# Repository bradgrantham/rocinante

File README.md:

# Introduction

I wired up a microcontroller on a protoboard to display video on a vintage CRT TV.

I call it Rocinante.

It's named after Don Quixote's horse in the novel by Miguel de Cervantes. Quixote is proud of his horse and views Rocinante as his noble steed that carries him boldy into battle.  Like Don Quixote, Rocinante is actually awkward, past his prime, and engaged in a task beyond his capabilities.

I reached the limit of what I could do comfortably on a protoboard, so I designed a PCB with the peripherals I thought I might need for a beefy version of the thing.  I had PCBWay make the boards and place the SMD parts.  The boards arrived November 4th, 2020.  I installed the through-hole parts myself.

# Hardware Features
* STM32H743IITX
* Power LED, debug LED, and RESET button
* BOOT button to reset into DFU mode
* 10-pin SWD (serial wire debugging) header
* USB connector for programming/device/host
* NTSC Composite video output
* Stereo audio output
* 3 "USER" buttons
* 3 programmable RGB LEDs (WS2812B aka "NeoPixel") and 3-pin header for chaining more
* Stereo audio input (untested)
* 2x PS/2 input (mouse, keyboard) (untested)
* 16-bit (R5G6B5) VGA output (untested)
* 166MHz 16MByte SDRAM (untested)
* 8-pin header compatible with ESP-01 for wireless (untested)
* SD card (untested)
* Expansion header with SPI and 2 GPIO
* I2S header

I'm keeping a spreadsheet of [the status of hardware features](https://docs.google.com/spreadsheets/d/15A8a8_nsbp0DDcee_6BzvSB4MXrgqT0VfsGb4YH8E2E/edit#gid=0) as I bring them up.

I'm keeping rework notes for Rev1 in [rework.md](rework.md).

# The Fundamental Idea

There is no framebuffer being directly scanned out in Rocinante.

Instead, there are two scanline buffers, and the CPU fills the next scanline buffer while DMA is scanning out the current scanline buffer.

Modern microcontrollers have high capabilities (the STM32H7 runs at 480MHz and has an FPU including double floats).  Embedded SRAM remains expensive, however, so most of the STM32 series doesn't contain enough RAM to display e.g. double-buffered 640x480 with 8-bit pixels.

This implementation trades CPU for memory and generates video data on-the-fly (aka "racing the beam") from a handful of different video formats at the time of writing:

* 1, 2, 4, and 8-bit palettized pixmaps
*  Monochrome text
* A "Wolfenstein"-style ray-casting maze renderer
* A display made of multiple run-length-compressed gradient spans per scanline

The current hardware supports a composite video display using NTSC output on an 8-bit DAC.  The pixel clock is 4x the color burst frequency, so typical console displays of the 1970's and 1980's should be almost directly representable.  Because the data is generated one scanline ahead and some CPU capacity is left over per scanline for apps, the latency for processing can be as low as one scanline.

Applications currently include a PPM viewer, PCM audio player, rudimentary 3D model viewer, and a very limited command shell.

I originally designed this with emulation of the Apple ][, ColecoVision, and Atari 2600 in mind, but who knows if I'll ever find the time for those!

# The Vision

## Hardware

On the PCB I also laid out a bunch of pie-in-the-sky features without knowing they would work.

The protoboard version used SPI to talk to an SD card.  The PCB wires an SD slot to the actual SDMMC signals on the STM32H7.

There's a 15-pin VGA header, two PS/2 jacks, and stereo audio input to give it some better media capabilities.

I daydreamed a system capable of running multiple simultaneous apps and installed 16 megabytes of SDRAM.

## Pipe Dream

Over time I hope I can make most of the system function.  If there's something that doesn't work but a fix is clear, maybe I'll spin a second rev of the board if I don't lose interest before then.

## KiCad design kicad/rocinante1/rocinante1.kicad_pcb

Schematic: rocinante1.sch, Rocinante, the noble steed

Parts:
BT1: 1225; BatteryHolder_Keystone_3001_1x12mm; Manufacturer PN 3001
C1, C2, C4, C6, C7, C8, C9, C10, C11, C12, C13, C14, C15, C16, C17, C21, C22, C23, C24, C28, C31, C32: 100nF; C_0603_1608Metric
C3, C5: 2.2µF; C_0603_1608Metric
C18, C19: 70nF; C_0603_1608Metric
C20: 1nF; C_0603_1608Metric
C25, C26, C27: 10µF; C_0603_1608Metric
C29, C30: 5.1pF; C_0603_1608Metric
C33, C35, C36: 1µF; C_0603_1608Metric
C34: 4.7µF; C_0603_1608Metric
D1: POWERLED; LED_0603_1608Metric; Manufacturer PN 150060GS75000
D2: DEBUGLED; LED_0603_1608Metric; Manufacturer PN 150060RS75000
D4: RGBLED1; LED_WS2812B_PLCC4_5.0x5.0mm_P3.2mm; Manufacturer PN WS2812B
D5: RGBLED2; LED_WS2812B_PLCC4_5.0x5.0mm_P3.2mm; Manufacturer PN WS2812B
D6: RGBLED3; LED_WS2812B_PLCC4_5.0x5.0mm_P3.2mm; Manufacturer PN WS2812B
F1: F_Small; Fuse_1210_3225Metric; Manufacturer PN 0ZCH0050FF2G
H1: HOLE0; MountingHole_3.2mm_M3_Pad_Via
H2: HOLE1; MountingHole_3.2mm_M3_Pad_Via
H3: HOLE2; MountingHole_3.2mm_M3_Pad_Via
H4: HOLE3; MountingHole_3.2mm_M3_Pad_Via
J1: ESP_01; PinSocket_2x04_P2.54mm_Vertical
J2: SWD; PinHeader_2x05_P1.27mm_Vertical_SMD; Manufacturer PN 20021521-00010C1LF
J3: COMPOSITE; CUI_RCJ-044; Manufacturer PN RCJ-044
J4: CTRL1; DSUB-9_Male_Horizontal_P2.77x2.84mm_EdgePinOffset7.70mm_Hou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; Manufacturer PN A-DS 09 A/KG-T2S
J5: CTRL2; DSUB-9_Male_Horizontal_P2.77x2.84mm_EdgePinOffset7.70mm_Hou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; Manufacturer PN A-DS 09 A/KG-T2S
J6: VGA; HD15-SN-24; Manufacturer PN HD15-SN-24
J7: AUDIOIN; Jack_3.5mm_CUI_SJ1-3535NG_Horizontal
J8: AUDIOOUT; Jack_3.5mm_CUI_SJ1-3535NG_Horizontal
J9: MOUSE; CUI_MD-60SM
J10: KEYBOARD; CUI_MD-60SM
J11: SERIAL; PinHeader_1x06_P2.54mm_Vertical
J12: SD_Card; 10067847-001RLF; Manufacturer PN 10067847-001RLF
J13: USBFS/POWER; USB_Micro-B_Amphenol_10104110_Horizontal; Manufacturer PN 10104110-0001LF
J14: I2S; PinHeader_1x06_P2.54mm_Vertical
J15: NEOPIXEL; PinHeader_1x03_P2.54mm_Vertical
J16: EXPHDR; PinHeader_2x05_P2.54mm_Vertical
Q1: Q_NPN_CBE; SOT-323_SC-70; Manufacturer PN MMBT3904WT1G
R1, R4: 220; R_0603_1608Metric
R2, R20, R28, R34: 2.2k; R_0603_1608Metric
R3: 6.8k; R_0603_1608Metric
R5: 215; R_0603_1608Metric
R6: 430; R_0603_1608Metric
R7: 860; R_0603_1608Metric
R8: 1.7k; R_0603_1608Metric
R9: 3.4k; R_0603_1608Metric
R10: 6.9k; R_0603_1608Metric
R11: 14k; R_0603_1608Metric
R12: 28K; R_0603_1608Metric
R13: 47; R_0603_1608Metric
R14, R15, R16, R21, R36, R37, R38, R39: 10K; R_0603_1608Metric
R17, R25, R31: 270; R_0603_1608Metric
R18, R26, R32: 560; R_0603_1608Metric
R19, R27, R33: 1100; R_0603_1608Metric
R22, R23, R43, R44, R45, R46, R47, R48: 20K; R_0603_1608Metric
R24, R29, R35: 4.3k; R_0603_1608Metric
R30: 8.6k; R_0603_1608Metric
R40, R41, R42: 150; R_0603_1608Metric
R49, R50, R51, R52, R53, R54: 68K; R_0603_1608Metric
R55, R56, R57, R58, R59, R60: 22; R_0603_1608Metric
R61, R62: 0; R_0603_1608Metric
SW1: RESET; SW_Push_1P1T_NO_6x6mm_H9.5mm; Manufacturer PN PTS645SM70SMTR92
SW2: USER1; SW_Push_1P1T_NO_6x6mm_H9.5mm; Manufacturer PN PTS645SM70SMTR92
SW3: USER2; SW_Push_1P1T_NO_6x6mm_H9.5mm; Manufacturer PN PTS645SM70SMTR92
SW4: USER3; SW_Push_1P1T_NO_6x6mm_H9.5mm; Manufacturer PN PTS645SM70SMTR92
SW5: BOOT0; SW_Push_1P1T_NO_6x6mm_H9.5mm; Manufacturer PN PTS645SM70SMTR92
TP1: CPST; TestPoint_Keystone_5015_Micro-Minature; Manufacturer PN RCW-0C
TP2: 5V; TestPoint_Keystone_5015_Micro-Minature; Manufacturer PN RCW-0C
TP3: 3V3; TestPoint_Keystone_5015_Micro-Minature; Manufacturer PN RCW-0C
TP4: GND; TestPoint_Keystone_5015_Micro-Minature; Manufacturer PN RCW-0C
TP5: KBDDATA; TestPoint_Keystone_5015_Micro-Minature; Manufacturer PN RCW-0C
TP6: KBDCLK; TestPoint_Keystone_5015_Micro-Minature; Manufacturer PN RCW-0C
U1: STM32H743IITx; LQFP-176_24x24mm_P0.5mm; Manufacturer PN STM32H743IIT6
U2: W9812G6KH-6; TSOP-II-54_22.2x10.16mm_P0.8mm; Manufacturer PN W9812G6KH-6
U3: LD1117S33TR_SOT223; SOT-223-3_TabPin2; Manufacturer PN LD1117S33TR
X1: ASE-14.31818MHz; Oscillator_SMD_Abracon_ASE-4Pin_3.2x2.5mm; Manufacturer PN ASEMB-14.31818MHZ-XY-T
Y1: 25MHz; Crystal_SMD_2016-4Pin_2.0x1.6mm; Manufacturer PN NX2016SA-25MHZ-EXS00A-CS11321

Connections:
ADC1_INP3: J7.T, U1.52
ADC1_INP5: J7.R, U1.57
ADC3_INP2: J4.9, U1.27
ADC3_INP3: J4.5, U1.25
ADC3_INP6: J5.9, U1.28
ADC3_INP7: J5.5, U1.26
AUDIO_OUT_L: C23.1, J8.T, R43.1
AUDIO_OUT_R: C24.1, J8.R, R44.1
BAT: BT1.1, C36.2, U1.6
BOOT: R21.1, SW5.2, U1.166
CLOCK0: R62.2, U1.29
CLOCK1: R61.2, U1.30
CV0: R12.2, U1.131
CV1: R11.2, U1.132
CV2: R10.2, U1.133
CV3: R9.2, U1.134
CV4: R8.2, U1.173
CV5: R7.2, U1.174
CV6: R6.2, U1.175
CV7: R5.2, U1.176
DAC1_OUT1: R22.2, U1.50
DAC1_OUT2: R23.2, U1.51
DEBUG: R4.1, U1.4
E1: J4.4, U1.86
E2: J5.4, U1.130
ESP_CH_EN: J1.4, U1.111
ESP_GPIO0: J1.5, R14.1
ESP_GPIO2: J1.3, R15.1
ESP_RST: J1.6, U1.110
ESP_RX: J1.7, U1.168
ESP_TX: J1.2, U1.11
EXPGPIO0: J16.8, U1.144
EXPGPIO1: J16.9, U1.145
EXPPWM: J16.7, U1.24
FIRE1: J4.6, U1.12
FIRE2: J5.6, U1.13
GND: BT1.2, C1.2, C2.2, C3.2, C4.2, C5.2, C6.2, C7.2, C8.2, C9.2, C10.2, C11.2, C12.2, C13.2, C14.2, C15.2, C16.2, C17.2, C18.2, C19.2, C20.2, C21.1, C22.1, C25.2, C26.2, C27.2, C28.1, C29.1, C30.1, C31.2, C32.1, C33.1, C34.2, C35.1, C36.1, D1.1 (K), D2.1 (K), D4.3, D5.3, D6.3, H1.1, H2.1, H3.1, H4.1, J1.1, J2.3, J2.5, J2.9, J4.0 (PAD), J5.0 (PAD), J6.0, J6.5, J6.6, J6.7, J6.8, J6.10, J7.S, J8.S, J9.3, J9.S1, J9.S2, J9.S3, J10.3, J10.S1, J10.S2, J10.S3, J11.6, J12.3, J12.6, J12.12, J12.13, J13.4, J13.5, J13.6, J14.6, J15.3, J16.6, R21.2, R40.1, R41.1, R42.1, R43.2, R44.2, SW1.1, TP4.1, U1.14, U1.22, U1.37, U1.48, U1.61, U1.71, U1.90, U1.102, U1.113, U1.126, U1.135, U1.148, U1.158, U2.6, U2.12, U2.28, U2.41, U2.46, U2.52, U2.54, U3.1, X1.2
I2C1_SCL: J6.15, U1.167
I2C1_SDA: J6.12, U1.165
I2S1_SDO: J14.3, U1.53
I2S_CK: J14.5, U1.154
I2S_SDI: J14.2, U1.152
I2S_WS: J14.4, U1.153
JOYSELECT: J4.7, J5.7, U1.58
KBD_CLK: J10.5, R38.1, R45.1, TP6.1
KBD_DATA: J10.1, R36.1, R46.1, TP5.1
KEYSELECT: J4.8, J5.8, U1.93
MOUSE_CLK: J9.5, R16.1, R47.1
MOUSE_DATA: J9.1, R37.1, R48.1
N1: J4.1, U1.83
N2: J5.1, U1.89
NRST: J2.10, SW1.2, U1.31
unnamed: C3.1, U1.125
unnamed: C5.1, U1.81
unnamed: C21.2, C23.2, R22.1
unnamed: C22.2, C24.2, R23.1
unnamed: C29.2, R61.1, Y1.1
unnamed: C30.2, R62.1, Y1.2
unnamed: D1.2 (A), R1.2
unnamed: D2.2 (A), R4.2
unnamed: D4.2, D5.4
unnamed: D4.4, Q1.1, R3.1
unnamed: D5.2, D6.4
unnamed: D6.2, J15.2
unnamed: F1.1, J13.1
unnamed: J12.1, R56.1
unnamed: J12.2, R57.1
unnamed: J12.5, R58.1
unnamed: J12.7, R59.1
unnamed: J12.8, R60.1
unnamed: J12.9, R55.1
unnamed: Q1.2, R2.1
unnamed: R39.1, X1.1
RGBLED_PWM: Q1.3, U1.5, U1.101
S1: J4.2, U1.84
S2: J5.2, U1.128
SDIO_CD: J12.10, U1.106
SDIO_CLK: R52.1, R58.2, U1.150
SDIO_CMD: R51.1, R57.2, U1.151
SDIO_D0: R53.1, R59.2, U1.94
SDIO_D1: R54.1, R60.2, U1.95
SDIO_D2: R49.1, R55.2, U1.161
SDIO_D3: R50.1, R56.2, U1.162
SDIO_WP: J12.11, U1.56
SDRAM_A0: U1.16, U2.23
SDRAM_A1: U1.17, U2.24
SDRAM_A2: U1.18, U2.25
SDRAM_A3: U1.19, U2.26
SDRAM_A4: U1.20, U2.29
SDRAM_A5: U1.21, U2.30
SDRAM_A6: U1.60, U2.31
SDRAM_A7: U1.63, U2.32
SDRAM_A8: U1.64, U2.33
SDRAM_A9: U1.65, U2.34
SDRAM_A10: U1.66, U2.22
SDRAM_A11: U1.67, U2.35
SDRAM_BA0: U1.108, U2.20
SDRAM_BA1: U1.109, U2.21
SDRAM_D0: U1.104, U2.2
SDRAM_D1: U1.105, U2.4
SDRAM_D2: U1.142, U2.5
SDRAM_D3: U1.143, U2.7
SDRAM_D4: U1.68, U2.8
SDRAM_D5: U1.69, U2.10
SDRAM_D6: U1.70, U2.11
SDRAM_D7: U1.73, U2.13
SDRAM_D8: U1.74, U2.42
SDRAM_D9: U1.75, U2.44
SDRAM_D10: U1.76, U2.45
SDRAM_D11: U1.77, U2.47
SDRAM_D12: U1.78, U2.48
SDRAM_D13: U1.96, U2.50
SDRAM_D14: U1.97, U2.51
SDRAM_D15: U1.98, U2.53
SDRAM_NBL0: U1.169, U2.15
SDRAM_NBL1: U1.170, U2.39
SDRAM_SDCKE0: U1.43, U2.37
SDRAM_SDCLK: U1.112, U2.38
SDRAM_SDNCAS: U1.160, U2.17
SDRAM_SDNE0: U1.44, U2.19
SDRAM_SDNRAS: U1.59, U2.18
SDRAM_SDNWE: U1.46, U2.16
SPI6_MISO: J16.1, U1.155
SPI6_MOSI: J16.4, U1.157
SPI6_NSS_SWCTL: J16.5, U1.107
SPI6_SCK: J16.3, U1.156
SWCLK: J2.4, U1.137
SWDIO: J2.2, U1.124
TIM1_CH2: U1.120, X1.3
TIM2_CH1: R45.2, U1.119, U1.138
TIM3_CH2: R47.2, U1.92, U1.163
TIM4_CH1: J6.13, U1.100
TIM5_CH2: J6.14, U1.88
USART1_RX: R46.2, U1.121, U1.164
USART2_CTS: J11.5, U1.40
USART2_RTS: U1.41
USART2_RX: J11.3, U1.47
USART2_TX: J11.2, U1.42
USART3_RX: R48.2, U1.79, U1.80
USB_FS_D_N: J13.2, U1.122
USB_FS_D_P: J13.3, U1.123
USER1: SW2.2, U1.1
USER2: SW3.2, U1.2
USER3: SW4.2, U1.3
VDD: C1.1, C2.1, C4.1, C6.1, C7.1, C8.1, C9.1, C10.1, C11.1, C12.1, C13.1, C14.1, C15.1, C16.1, C17.1, C18.1, C19.1, C25.1, C27.1, C31.1, C34.1, C35.2, J1.8, J2.1, J12.4, J14.1, J16.2, R1.1, R2.2, R13.1, R14.2, R15.2, R39.2, R49.2, R50.2, R51.2, R52.2, R53.2, R54.2, SW2.1, SW3.1, SW4.1, SW5.1, TP3.1, U1.15, U1.23, U1.36, U1.39, U1.49, U1.62, U1.72, U1.82, U1.91, U1.103, U1.114, U1.127, U1.136, U1.149, U1.159, U1.171, U1.172, U2.1, U2.3, U2.9, U2.14, U2.27, U2.43, U2.49, U3.2, X1.4
VGA_B0: R24.2, U1.32
VGA_B1: R20.2, U1.33
VGA_B2: R19.2, U1.34
VGA_B3: R18.2, U1.35
VGA_B4: R17.2, U1.54
VGA_BLUE: J6.3, R17.1, R18.1, R19.1, R20.1, R24.1, R40.2
VGA_G0: R30.2, U1.55
VGA_G1: R29.2, U1.115
VGA_G2: R28.2, U1.116
VGA_G3: R27.2, U1.117
VGA_G4: R26.2, U1.118
VGA_G5: R25.2, U1.139
VGA_GREEN: J6.2, R25.1, R26.1, R27.1, R28.1, R29.1, R30.1, R41.2
VGA_ID0: J6.11
VGA_ID2: J6.4
VGA_R0: R35.2, U1.140
VGA_R1: R34.2, U1.141
VGA_R2: R33.2, U1.8
VGA_R3: R32.2, U1.9
VGA_R4: R31.2, U1.10
VGA_RED: J6.1, R31.1, R32.1, R33.1, R34.1, R35.1, R42.2
VREFP: C32.2, C33.2, R13.2, U1.38
W1: J4.3, U1.85
W2: J5.3, U1.129

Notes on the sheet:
Compatible with Jim’s SPI header on pins 1-6
VDD DECOUPLING

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
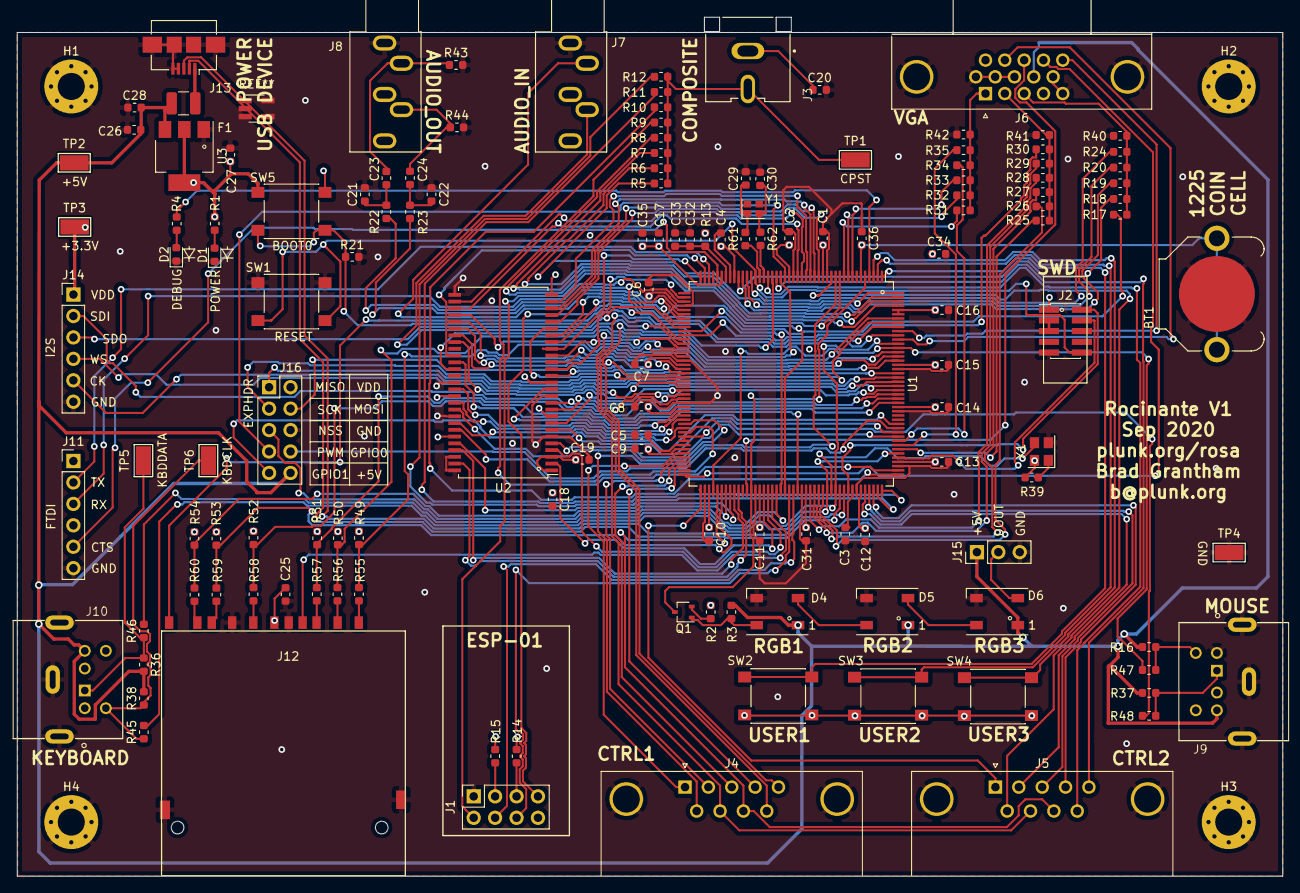
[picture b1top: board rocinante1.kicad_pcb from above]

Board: 4 copper layers, 150.0 x 101.8 mm, 142 parts (0 on the bottom side), 169 nets.

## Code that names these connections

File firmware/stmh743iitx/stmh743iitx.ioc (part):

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Mcu.Name=STM32H743IITx
Mcu.Package=LQFP176
Mcu.UserName=STM32H743IITx
PA0.Mode=CTS_RTS
PA0.Signal=USART2_CTS
PA1.Mode=CTS_RTS
PA1.Signal=USART2_RTS
PA10.Mode=Synchronous Slave
PA10.Signal=USART1_RX
PA11.Mode=Device_Only
PA11.Signal=USB_OTG_FS_DM
PA12.Mode=Device_Only
PA12.Signal=USB_OTG_FS_DP
PA13\ (JTMS/SWDIO).Mode=Serial_Wire
PA13\ (JTMS/SWDIO).Signal=DEBUG_JTMS-SWDIO
PA14\ (JTCK/SWCLK).Mode=Serial_Wire
PA14\ (JTCK/SWCLK).Signal=DEBUG_JTCK-SWCLK
PA15\ (JTDI).Signal=S_TIM2_CH1
PA2.Mode=Asynchronous
PA2.Signal=USART2_TX
PA3.Mode=Asynchronous
PA3.Signal=USART2_RX
PA4.Signal=COMP_DAC11_group
PA5.Signal=COMP_DAC12_group
PA6.Signal=ADCx_INP3
PA7.Mode=Full_Duplex_Master
PA7.Signal=I2S1_SDO
PA8.Mode=Synchronous Slave
PA8.Signal=USART1_CK
PA9.Signal=S_TIM1_CH2
PB0.Signal=GPIO_Input
PB1.Signal=ADCx_INP5
PB10.Mode=Synchronous Slave
PB10.Signal=USART3_TX
PB11.Mode=Synchronous Slave
PB11.Signal=USART3_RX
PB12.Mode=Synchronous Slave
PB12.Signal=USART3_CK
PB14.Mode=SD_4_bits_Wide_bus
PB14.Signal=SDMMC2_D0
PB15.Mode=SD_4_bits_Wide_bus
PB15.Signal=SDMMC2_D1
PB3\ (JTDO/TRACESWO).Mode=SD_4_bits_Wide_bus
PB3\ (JTDO/TRACESWO).Signal=SDMMC2_D2
PB4\ (NJTRST).Mode=SD_4_bits_Wide_bus
PB4\ (NJTRST).Signal=SDMMC2_D3
PB5.Signal=S_TIM3_CH2
PB6.Mode=Synchronous Slave
PB6.Signal=USART1_TX
PB7.Mode=I2C
PB7.Signal=I2C1_SDA
PB8.Mode=I2C
PB8.Signal=I2C1_SCL
PB9.Mode=Asynchronous
PB9.Signal=UART4_TX
PC0.Signal=GPIO_Output
PC1.Signal=GPIO_Output
PC10.Signal=GPIO_Output
PC11.Signal=GPIO_Output
PC12.Signal=GPIO_Output
PC13.Signal=GPIO_Output
PC14-OSC32_IN\ (OSC32_IN).Signal=GPIO_Output
PC15-OSC32_OUT\ (OSC32_OUT).Signal=GPIO_Output
PC2_C.Signal=GPIO_Output
PC3_C.Signal=GPIO_Output
PC4.Signal=GPIO_Output
PC5.Signal=GPIO_Output
PC6.Signal=GPIO_Output
PC7.Signal=GPIO_Output
PC8.Signal=GPIO_Output
PC9.Signal=GPIO_Output
PD0.Signal=FMC_D2_DA2
PD1.Signal=FMC_D3_DA3
PD10.Signal=FMC_D15_DA15
PD12.Signal=S_TIM4_CH1
PD13.Signal=S_TIM4_CH2
PD14.Signal=FMC_D0_DA0
PD15.Signal=FMC_D1_DA1
PD6.Mode=SD_4_bits_Wide_bus
PD6.Signal=SDMMC2_CK
PD7.Mode=SD_4_bits_Wide_bus
PD7.Signal=SDMMC2_CMD
PD8.Signal=FMC_D13_DA13
PD9.Signal=FMC_D14_DA14
PE0.Signal=FMC_NBL0
PE1.Signal=FMC_NBL1
PE10.Signal=FMC_D7_DA7
PE11.Signal=FMC_D8_DA8
PE12.Signal=FMC_D9_DA9
PE13.Signal=FMC_D10_DA10
PE14.Signal=FMC_D11_DA11
PE15.Signal=FMC_D12_DA12
PE2.Signal=GPXTI2
PE3.Signal=GPXTI3
PE4.Signal=GPXTI4
PE5.Signal=S_TIM15_CH1
PE6.Signal=S_TIM15_CH2
PE7.Signal=FMC_D4_DA4
PE8.Signal=FMC_D5_DA5
PE9.Signal=FMC_D6_DA6
PF0.Signal=FMC_A0
PF1.Signal=FMC_A1
PF10.Mode=IN6-Single-Ended
PF10.Signal=ADC3_INP6
PF11.Signal=FMC_SDNRAS
PF12.Signal=FMC_A6
PF13.Signal=FMC_A7
PF14.Signal=FMC_A8
PF15.Signal=FMC_A9
PF2.Signal=FMC_A2
PF3.Signal=FMC_A3
PF4.Signal=FMC_A4
PF5.Signal=FMC_A5
PF7.Mode=IN3-Single-Ended
PF7.Signal=ADC3_INP3
PF8.Mode=IN7-Single-Ended
PF8.Signal=ADC3_INP7
PF9.Mode=IN2-Single-Ended
PF9.Signal=ADC3_INP2
PG0.Signal=FMC_A10
PG1.Signal=FMC_A11
PG10.Mode=Full_Duplex_Master
PG10.Signal=I2S1_WS
PG11.Mode=Full_Duplex_Master
PG11.Signal=I2S1_CK
PG12.Mode=Full_Duplex_Master
PG12.Signal=SPI6_MISO
PG13.Mode=Full_Duplex_Master
PG13.Signal=SPI6_SCK
PG14.Mode=Full_Duplex_Master
PG14.Signal=SPI6_MOSI
PG15.Signal=FMC_SDNCAS
PG2.Signal=GPIO_Input
PG3.Signal=GPIO_Output
PG4.Signal=FMC_A14_BA0
PG5.Signal=FMC_A15_BA1
PG6.Signal=GPIO_Output
PG7.Signal=GPIO_Output
PG8.Signal=FMC_SDCLK
PG9.Mode=Full_Duplex_Master
PG9.Signal=I2S1_SDI
PH0-OSC_IN\ (PH0).Mode=HSE-External-Oscillator
PH0-OSC_IN\ (PH0).Signal=RCC_OSC_IN
PH1-OSC_OUT\ (PH1).Mode=HSE-External-Oscillator
PH1-OSC_OUT\ (PH1).Signal=RCC_OSC_OUT
PH11.Signal=S_TIM5_CH2
PH12.Signal=GPXTI12
PH13.Signal=GPXTI13
PH14.Signal=GPXTI14
PH15.Signal=GPXTI15
PH2.Mode=SdramChipSelect1_1
PH2.Signal=FMC_SDCKE0
PH3.Mode=SdramChipSelect1_1
PH3.Signal=FMC_SDNE0
PH5.Signal=FMC_SDNWE
PH6.Signal=GPXTI6
PH7.Signal=GPXTI7
PH8.Signal=GPXTI8
PH9.Signal=GPXTI9
PI0.Signal=GPIO_Output
PI1.Signal=GPIO_Output
PI2.Signal=GPIO_Output
PI3.Signal=GPIO_Output
PI4.Signal=GPIO_Output
PI5.Signal=GPIO_Output
PI6.Signal=GPIO_Output
PI7.Signal=GPIO_Output
PI9.Mode=Asynchronous
PI9.Signal=UART4_RX
RCC.SYSCLKFreq_VALUE=64000000
board=custom

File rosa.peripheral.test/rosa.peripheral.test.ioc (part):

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Mcu.Name=STM32H743IITx
Mcu.Package=LQFP176
Mcu.UserName=STM32H743IITx
PA11.Mode=Host_Only
PA11.Signal=USB_OTG_FS_DM
PA12.Mode=Host_Only
PA12.Signal=USB_OTG_FS_DP
PA13\ (JTMS/SWDIO).Mode=Serial_Wire
PA13\ (JTMS/SWDIO).Signal=DEBUG_JTMS-SWDIO
PA14\ (JTCK/SWCLK).Mode=Serial_Wire
PA14\ (JTCK/SWCLK).Signal=DEBUG_JTCK-SWCLK
PA15\ (JTDI).Signal=S_TIM2_CH1
PA2.Mode=Asynchronous
PA2.Signal=USART2_TX
PA3.Mode=Asynchronous
PA3.Signal=USART2_RX
PA9.GPIOParameters=GPIO_Speed
PA9.GPIO_Speed=GPIO_SPEED_FREQ_VERY_HIGH
PA9.Signal=S_TIM1_CH2
PB14.Mode=SD_4_bits_Wide_bus
PB14.Signal=SDMMC2_D0
PB15.Mode=SD_4_bits_Wide_bus
PB15.Signal=SDMMC2_D1
PB3\ (JTDO/TRACESWO).Mode=SD_4_bits_Wide_bus
PB3\ (JTDO/TRACESWO).Signal=SDMMC2_D2
PB4\ (NJTRST).Mode=SD_4_bits_Wide_bus
PB4\ (NJTRST).Signal=SDMMC2_D3
PB6.Signal=USART1_TX
PC0.Signal=FMC_SDNWE
PC2_C.Mode=SdramChipSelect1_1
PC2_C.Signal=FMC_SDNE0
PC3_C.Mode=SdramChipSelect1_1
PC3_C.Signal=FMC_SDCKE0
PD0.Signal=FMC_D2_DA2
PD1.Signal=FMC_D3_DA3
PD10.Signal=FMC_D15_DA15
PD14.Signal=FMC_D0_DA0
PD15.Signal=FMC_D1_DA1
PD6.Mode=SD_4_bits_Wide_bus
PD6.Signal=SDMMC2_CK
PD7.Mode=SD_4_bits_Wide_bus
PD7.Signal=SDMMC2_CMD
PD8.Signal=FMC_D13_DA13
PD9.Signal=FMC_D14_DA14
PE0.Signal=FMC_NBL0
PE1.Signal=FMC_NBL1
PE10.Signal=FMC_D7_DA7
PE11.Signal=FMC_D8_DA8
PE12.Signal=FMC_D9_DA9
PE13.Signal=FMC_D10_DA10
PE14.Signal=FMC_D11_DA11
PE15.Signal=FMC_D12_DA12
PE2.Mode=TX_Only_Simplex_Unidirect_Master
PE2.Signal=SPI4_SCK
PE3.GPIOParameters=GPIO_PuPd,GPIO_Label
PE3.GPIO_Label=USER2
PE3.GPIO_PuPd=GPIO_PULLDOWN
PE3.Signal=GPIO_Input
PE4.GPIOParameters=GPIO_PuPd,GPIO_Label
PE4.GPIO_Label=USER3
PE4.GPIO_PuPd=GPIO_PULLDOWN
PE4.Signal=GPIO_Input
PE5.GPIOParameters=GPIO_Label
PE5.GPIO_Label=DEBUG_LED
PE5.Signal=GPIO_Output
PE6.GPIOParameters=GPIO_Speed,GPIO_PuPd,GPIO_Label
PE6.GPIO_Label=RGBLED_SPI
PE6.GPIO_PuPd=GPIO_PULLDOWN
PE6.GPIO_Speed=GPIO_SPEED_FREQ_HIGH
PE6.Mode=TX_Only_Simplex_Unidirect_Master
PE6.Signal=SPI4_MOSI
PE7.Signal=FMC_D4_DA4
PE8.Signal=FMC_D5_DA5
PE9.Signal=FMC_D6_DA6
PF0.Signal=FMC_A0
PF1.Signal=FMC_A1
PF11.Signal=FMC_SDNRAS
PF12.Signal=FMC_A6
PF13.Signal=FMC_A7
PF14.Signal=FMC_A8
PF15.Signal=FMC_A9
PF2.Signal=FMC_A2
PF3.Signal=FMC_A3
PF4.Signal=FMC_A4
PF5.Signal=FMC_A5
PG0.Signal=FMC_A10
PG1.Signal=FMC_A11
PG15.Signal=FMC_SDNCAS
PG2.GPIOParameters=GPIO_PuPd,GPIO_Label
PG2.GPIO_Label=SDIO_CD
PG2.GPIO_PuPd=GPIO_PULLUP
PG2.Signal=GPIO_Input
PG4.Signal=FMC_A14_BA0
PG5.Signal=FMC_A15_BA1
PG8.Signal=FMC_SDCLK
PH0-OSC_IN\ (PH0).Mode=HSE-External-Oscillator
PH0-OSC_IN\ (PH0).Signal=RCC_OSC_IN
PH1-OSC_OUT\ (PH1).Mode=HSE-External-Oscillator
PH1-OSC_OUT\ (PH1).Signal=RCC_OSC_OUT
PI0.GPIOParameters=GPIO_Speed
PI0.GPIO_Speed=GPIO_SPEED_FREQ_MEDIUM
PI0.Signal=GPIO_Output
PI1.GPIOParameters=GPIO_Speed
PI1.GPIO_Speed=GPIO_SPEED_FREQ_MEDIUM
PI1.Signal=GPIO_Output
PI2.GPIOParameters=GPIO_Speed
PI2.GPIO_Speed=GPIO_SPEED_FREQ_MEDIUM
PI2.Signal=GPIO_Output
PI3.GPIOParameters=GPIO_Speed
PI3.GPIO_Speed=GPIO_SPEED_FREQ_MEDIUM
PI3.Signal=GPIO_Output
PI4.GPIOParameters=GPIO_Speed
PI4.GPIO_Speed=GPIO_SPEED_FREQ_MEDIUM
PI4.Signal=GPIO_Output
PI5.GPIOParameters=GPIO_Speed
PI5.GPIO_Speed=GPIO_SPEED_FREQ_MEDIUM
PI5.Signal=GPIO_Output
PI6.GPIOParameters=GPIO_Speed
PI6.GPIO_Speed=GPIO_SPEED_FREQ_MEDIUM
PI6.Signal=GPIO_Output
PI7.GPIOParameters=GPIO_Speed
PI7.GPIO_Speed=GPIO_SPEED_FREQ_MEDIUM
PI7.Signal=GPIO_Output
RCC.SYSCLKFreq_VALUE=480000000
RCC.SYSCLKSource=RCC_SYSCLKSOURCE_PLLCLK
board=custom

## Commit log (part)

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2020-04-25 clean up
    use normal getchar and setvbuf for single-key input
    add variables to Makefile for compiling and adding microray
    retire DAC issue in notes , add some more TODOs
    use TIM9 in DMA IRQ Handler, clean up slightly
2020-04-25 remove SERIAL_flush
2020-04-25 specify flash is slow; fix microray variables
2020-04-25 be draconian with min heap size; will force less .data and .bss
2020-04-25 allow 4 files to reduce memory use
2020-04-25 putting scanling info in normal RAM doesn't make things worse
2020-04-27 enable TIM9
2020-04-27 hosted application driver; WIP
2020-04-27 Remove unnecessary SERIAL_flush
2020-04-27 Add some more notes on optimization
2020-04-28 add notes on filtering and threading
2020-04-28 make main.o a regular object, add separate wolftextures
2020-04-29 add waveforms of different frequencies
2020-04-29 add initial support for STM32F746
2020-04-30 get SD working; reenable FatFS
2020-05-02 make hosted vehicle C++
2020-05-02 return to previous stack carveout
2020-05-02 video works
2020-05-02 update to match TIM1 clock in STM324F746
2020-05-05 include the F7 version of the SDK
2020-05-05 enable dcache; enable audio; enable FIFO threshold; fix row cycle counts
2020-05-06 notes on GLFW integration
2020-05-08 use float for interpolants, needs speeding up
2020-05-12 add comparison of pixel rows fill by segments
2020-05-12 Add a segment test
2020-05-12 make everything take a ...Segment
2020-05-12 fix bug, add drawing spheres
2020-05-13 add and use segment pool
2020-05-13 use segment_utility for circles in segtest
2020-05-13 fix circles; add VideoBufferReset
2020-05-13 make new segment utilities
2020-05-20 move main to C++, restructure VRAM, improve show and segment test
    output slightly more correct clocks but still wrong in clocks.py
    make colorburst waveform more closely match Apple 2 by increasing number and moving slightly earlier
    fix incorrect args parsing in showimage.c
    print the largest allocatable before each command prompt
    beef up .gitignores
    add BASIC programs I'd like to run
2020-05-22 make all warnings cause an error
2020-05-22 remove incorrect RAM note
2020-06-04 Add missing files
2020-06-05 stub rasterization if not HOSTED
2020-06-06 fix GL lighting
2020-06-07 add notes on closing out segmented mode
2020-06-07 add depth buffering, name Rasterizer API better
2020-06-16 fix phrasing
2020-06-18 defer trapezoids from triangles; render trapezoids
2020-06-18 use smaller structs, delete unused code
2020-06-21 get some statistics on trapezoid segments; store in notes
2020-06-25 add lots more notes on windowing
2020-06-25 make array-list operations into member functions
2020-06-30 factor out IsEmpty, improve scanline check; better stats
2020-07-08 Add more models and converters, add aspect ratio, more segmented video
2020-08-16 remove old boot.bin target, add note about st-flash
2020-08-16 calculate target, add measured HSE
2020-08-16 Add more clocks for discovery mode
    Also Add aspect ratio of segmented video mode
    Also output HSE/5 on MCO2
2020-08-16 add 3D rendering through segments
2020-08-16 add binaries
2020-08-16 STM32H745IGTx library for KiCad
2020-08-18 add notes on ETR experiment
2020-08-30 use floats for better register availability
2020-08-30 add most of schematic for Rosa v1
2020-09-06 remove stray vi command
2020-09-08 finish schematic draft; place some parts
2020-09-13 put tests and tools in better-named directory
2020-09-13 checkpoint clocks script
2020-09-13 add DAC line but commented, note current DAC max
2020-09-13 add more notes
2020-09-14 add span windowing test
2020-09-19 add first revision of PCB
2020-09-21 add some necessary BOM fields
2020-09-23 factor out some ntsc and dac functionality
2020-10-06 Checkpoint video subsystem rewrite
    Move NTSC constants out
    Disable all but 40x24 text and 8-bit overscan mode temporarily
2020-10-09 checkpoint video rewrite
2020-10-10 Add de-chroma test
2020-10-10 add initial Window stubs
2020-10-11 add attempt at decoding NTSC signal at DAC
2020-10-20 checkpoint showimage work on video rewrite
2020-10-24 add draft spans in WindowCreate plus palette functions
2020-10-25 move to scanline ranges
2020-10-31 add window span code to hosted, disable old driver methods
2020-11-02 store NTSC structures in VRAM
2020-11-06 add Rosa bringup test program
2020-11-06 fix label placement
2020-11-06 USART2 test
2020-11-06 update to bringup of PCB
2020-11-07 checkpoint work on RGB LEDs; 3X SPI sort of working
2020-11-08 WS2812Bs demonstrated working
    Using blocking SPI transmit at the moment
    SPI4 uses PE2 and PE6, which means USER1 button isn't currently read.
    Demo
    RGB1 red on and off, cycling every second.
    RGB2 rotates through hue every pi*2 seconds
    RGB3 rises from off to white over one second and back to off over one second
2020-11-08 use lower max value for RGB animation test
2020-11-08 add V1 image
2020-11-08 additional demo images
2020-11-10 save failed PS/2 TIM experiments for reference
2020-11-12 add more lines of top-level docs brainstorm
2020-11-15 add GPIOI DAC test
2020-11-16 NTSC works marginally
2020-11-17 fix cap at composite out
2020-11-17 add rework notes
2020-11-17 fix link to rework
2020-11-17 add tool to make blob for composite scanout
2020-11-17 add video test - subject is Millie the dog
2020-11-18 Move to 912 samples to be a multiple of colorburst
2020-11-22 output a const array; more likely to go into ROM
2020-11-22 add ProcessYield prototype
2020-11-22 do interlaced NTSC
2020-11-22 add scale functions
2020-11-22 use scale functions in show app
2020-11-22 implement pixmap fillRow
2020-11-22 update notes
2020-11-24 fix crash by not using iterator
2020-11-24 put more debug guards around dumps and prints
2020-11-27 lay groundwork for moveAllocation
2020-11-28 make window status be or'd bitfields
    And add the ability to set maximum pixel scale in showimage
2020-11-30 Add mouse pointer and fix NTSC decoding
2020-12-05 checkpoint apple2e emulator hack
2020-12-05 clean up
    change sprintf(message) etc to printf
    turn on scanout mark
    optimize Woz HGR fillrow
    tell apple2 to go "-fast"
    some constexprs
    temporarily turn off audio fill
2020-12-06 initial notes; user buttons
2020-12-06 remove unused array, fix missing return value
2020-12-08 Add events and keyboard processing and tests
    Also add NTSC func ptr switch function and "valid" flag
    Maybe fix the strange colors in HGR mode
    Add text and HGR mode tests
2020-12-09 put into tree so that I know if MX changes this
2020-12-09 Add tools for experimenting with dithered Apple //e DHGR
2020-12-09 add mouse processing
    move keyboard.{cpp,h} to hid*
    Also enable SDMMC for next experiments
2020-12-10 update with SDMMC and FATFS
2020-12-10 add FATFS, SDMMC, and a test for SD
2020-12-12 increase heap
2020-12-13 Add rework for USER1
2020-12-13 make output const
2020-12-13 fix ampersand
2020-12-13 add initial keyboard support to apple2e
2020-12-13 keyboard fixes, interactive apple 2
    use key repeat manager
    launch apple2e emulator in interactive mode,
    don't prepopulate key buffer with program
    enable DMA for SPI4
    increase heap size in MX project to match hand-coded
2020-12-13 upgrade version
2020-12-13 more diffusion methods, vec3f type
2020-12-13 squelch ABI warning
2020-12-13 fix warning
2020-12-13 Fix some keyboard processing
    Fix keyboard release in apple2e
    Fix repeat processing idiom
    And clean up some warnings
    F12 is RESET in Apple2e
    LEFT Win (GUI) is left APPLE so Win-F12 is REBOOT
2020-12-14 fix CTRL in apple2e
2020-12-14 test audio; provide app LED interface
2020-12-15 add RoDebugOverlayPrintf, rename LEDSet, SDMMC divider 5
2020-12-15 clear floppy drive light on RESET
2020-12-20 Remove unused variable
2020-12-20 add my version of Jim's script for running gdb-server over SWD
2020-12-28 Make apple2e audio work and floppy fast,
    Fix code to avoid warnings
    Shrink heap slightly to fit data
    Update to main apple2e emulator source at 43c3c8a
    Update to improved cpu6502 emulator source at 43c3c8a
    Fix apple2e emulator audio by plumbing realtime buffer size through
    Make some arrays "const" hoping they'll stay in ROM
2021-01-02 implement GR; reduce memory use for Woz video modes
    store Woz TEXT and HGR buffers in scanline order; deinterleave in
    interface_rosa.cpp
    implement Woz GR mode
    reduce Woz buffer size to on-screen area
2021-01-02 import CPU updates from apple2e project
2021-01-02 add artifact bit pattern to color decoder
2021-01-03 implement DHGR
2021-01-04 fix spelling, remove pretentious wording
2021-01-04 connect arrow keys
2021-08-16 Rework to add 21.47277MHz base pixel clock
2021-08-16 work with GCC 10
2021-08-19 attempt SDRAM init
2021-12-26 checkpoint
2021-12-27 checkpoint VGA; image can be displayed
2021-12-29 add working SDRAM config and simple tests
2021-12-29 tune VGA tests; display from SDRAM
    Copy the ROM image to SDRAM
    Display from SDRAM
    Increase SDRAM clock speed
2021-12-30 use SDRAM at the right address and tune VGA scanout
2021-12-30 tune VGA more, start factoring out VGA functions
2021-12-30 make a constant for sysclock divider for VGA timing
2021-12-31 checkpoint VGA
2022-01-01 fix location of VGA - still not quite right
2022-01-01 improve VGA
2022-01-01 clean out breakdeadtime code, only draw on USER2
2022-01-03 temp passthrough to ESP-01, add more peripherals
2022-02-06 disable VGA and ESP-01 terminal
2022-02-07 add pointer ownership note
2022-02-07 drop back to div 6 for SD card
2022-02-07 implement Atari and Coleco joysticks and keypad
2022-02-08 extract controller test out of main, quiet warnings
2022-02-09 create NTSC from the TMS9918A RAM and registers
2022-02-12 make functions inline so they aren't multiply defined symbols
2022-02-14 fix playAudio by increasing audio buffer size
2022-02-14 update to desktop emulator master
2022-03-07 update to newest emulator code
2022-03-07 compile C version of z80emu
2022-03-07 fix compile error
2022-03-07 optimize TMS scanout slightly
2022-03-07 factor sprite inner loop into not-SIZE4 and SIZE4
2022-03-08 update to emulator source
2022-03-08 optimize TMS9918ModeFillRowBuffer, remove startup delay and print
2022-03-08 remove lazy updates of frame
2022-03-10 update to main emulator branch 219ee45
2022-04-20 update to main emulator branch 91d9438
2022-05-06 reduce number of max processes for events
2022-05-06 update to coleco 52fe530
2022-05-07 remove delays in controller reads
    Add delay_us function
    Change leading delays in controller I/O from 1 ms to 10 us
    Remove trailing delays in controller I/O
    Improve NTSCWaitFrame function
    Remove no longer used TMS9918 registers+memory graphics mode
    Remove playback of VDP test vectors
2022-05-07 change audio interface to a ring buffer
    Allow arbitrary writes into an audio ring buffer
    Coleco will work, Apple II and other modules won't
2022-05-08 update to original @5364a27
2022-05-19 add system-side console event queue handling
2022-05-20 add console button processing to line ISR
2022-05-20 plumb console buttons through to queue
2022-05-22 add initial mp3player; untested
2022-05-27 add button 2 quits
2022-10-17 lead in audio to avoid popping
2022-10-17 remove windowing; make lastTick be lastMilli
2022-10-18 cleanup
    remove buffer parameter from RoAudioGetSamplingInfo
    remove unused audio API
    change NTSCSwitchModeFuncs to NTSCSetModeFuncs
    add parameter for interlace to NTSCSetModeFuncs
    remove playAudio since it uses old audio API
    remove old hardcoded apple2e program inputs
2022-10-18 upgrade STM32CUBE version for programmer
2022-10-18 implement interlaced NTSC
2022-10-18 update rosa-apps for apple2e woz code
2022-10-18 make NTSC funcs usable from other compilation unit
2022-10-18 use apple2e and coleco in rosa-apps
2022-10-18 rename functions, make functions available
2022-10-18 get rid of ntsc constants
2022-10-18 Add Ro on front of Event
2022-10-18 remove straggler from apple2e
2022-10-18 update rosa-kit
2022-10-18 break out 8x16
2022-10-18 move UI functions into rosa-kit
2022-10-18 extract launcher as an app
2022-10-18 fix API race problem by combining functions
2022-10-18 elevate housekeeping to API call
2022-10-20 remove unused function
2022-10-20 add FATFS configuration
2022-10-21 don't reset video mode if it's the same parameters
2022-12-04 enable USB
2022-12-19 add lip for joining two halves
2022-12-19 add some connectors
2022-12-20 add bosses
2023-01-02 update including LED recesses
